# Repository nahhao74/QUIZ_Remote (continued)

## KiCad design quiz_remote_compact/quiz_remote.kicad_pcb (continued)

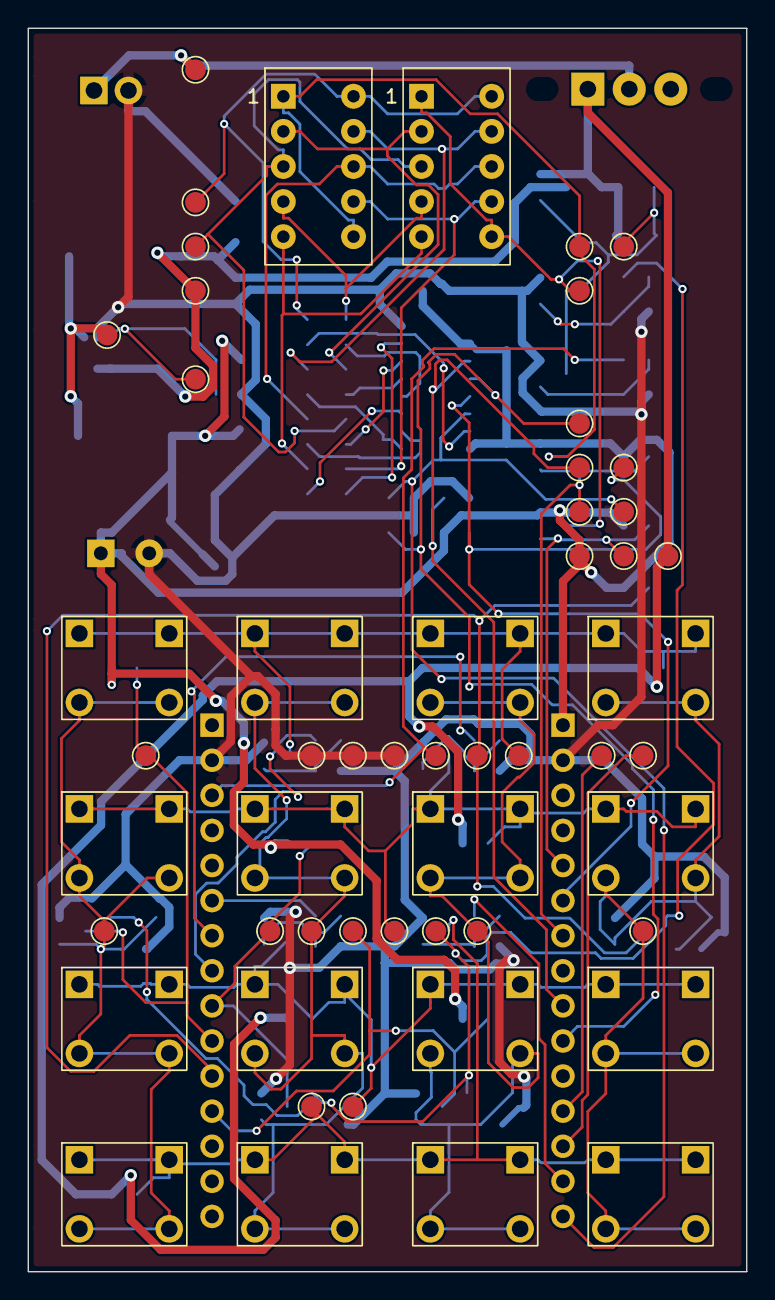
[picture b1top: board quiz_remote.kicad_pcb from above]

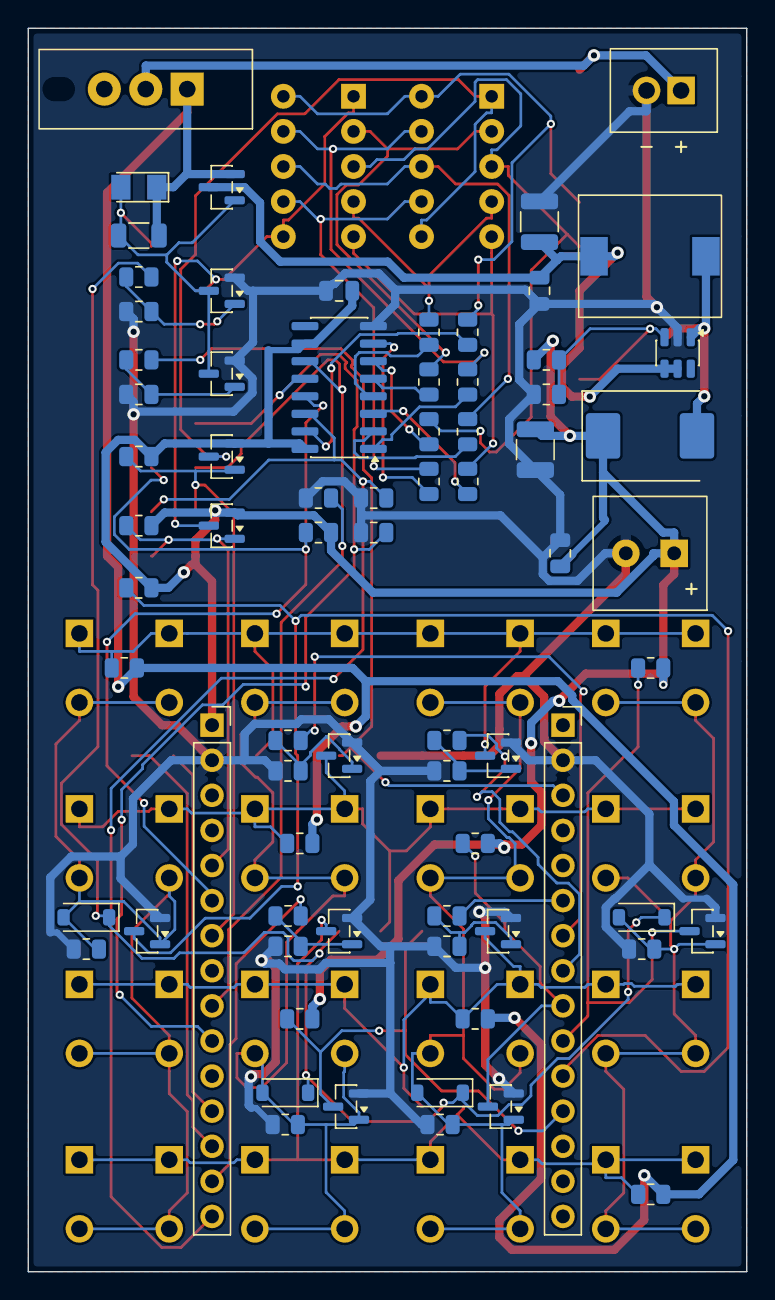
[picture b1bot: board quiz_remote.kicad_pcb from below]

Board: 2 copper layers, 52.0 x 90.0 mm, 127 parts (73 on the bottom side), 58 nets.

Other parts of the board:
C_GATE: 4.7uF; CP_AVX_TAJ_A_3216_18
JBAT: LK2114_BATTERY; JBAT_LK2114_P2.50_Prototype
QHOLD: MMBT3904; SOT-23
QPWR: AO3401A; SOT-23
QWAKE: MMBT3904; SOT-23
R_GATE: 220k; R_1206_3216Metric
R_HOLD: 10k; R_0805_2012Metric
R_HOLD_PD: 100k; R_0805_2012Metric
R_WAKE: 100k; R_0805_2012Metric
R_WAKE_PD: 1M; R_0805_2012Metric
SW_MAIN: SS-12F23G4; SW_SS12F23G4_LK
TP_GND: GND; TestPoint_Pad_D1.5mm
TP_PWR_GATE: PWR_GATE; TestPoint_Pad_D1.5mm
TP_VBAT_AON: VBAT_AON; TestPoint_Pad_D1.5mm
TP_VBAT_RAW: VBAT_RAW; TestPoint_Pad_D1.5mm

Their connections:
/M1_BATTERY_MAIN_SWITCH/VBAT_RAW: JBAT.1, SW_MAIN.2, TP_VBAT_RAW.1
/M2_POWER_GATE_WAKE_HOLD/PWR_GATE: C_GATE.2, QHOLD.3, QPWR.1, QWAKE.3, R_GATE.2, TP_PWR_GATE.1
/PWR_HOLD: R_HOLD.1; also elsewhere on the board
/VBAT_AON: C_GATE.1, QPWR.2, R_GATE.1, SW_MAIN.1, TP_VBAT_AON.1; also elsewhere on the board
/WAKE_NODE: R_WAKE.1; also elsewhere on the board
unnamed: QHOLD.1, R_HOLD.2, R_HOLD_PD.1
unnamed: QWAKE.1, R_WAKE.2, R_WAKE_PD.1
